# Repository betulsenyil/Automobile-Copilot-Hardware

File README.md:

# Automobile Copilot - Power & Motor Control System

This repository contains the hardware design files for an **Automobile Copilot System**. The project focuses on creating a reliable power management and motor actuation layer, specifically designed to handle the electrical environment of a vehicle.

## 📌 Project Overview
As a Computer Engineering student at Istanbul Sabahattin Zaim University, I developed this circuit to bridge the gap between high-level software logic and physical vehicle actuators. The board ensures clean power delivery to an Arduino Uno and provides safe control for DC motors.

## 🛠 Technical Specifications
- **Voltage Input:** +12V DC (Automotive battery compatible).
- **Voltage Regulation:** Integrated **LM2596** Switching Regulator (12V to 5V conversion).
- **Motor Driver:** **L298HN** Dual H-Bridge for bidirectional motor control.
- **Protection Circuits:**
  - **SMBJ16A TVS Diode:** Protects against transient voltage spikes common in vehicles.
  - **UF4007 Ultra-Fast Diodes:** Flyback protection against inductive back-EMF.
  - **Fused Input:** Integrated 1-2A fuse for overcurrent protection.

## 📂 File Structure
- [📄 Download Schematic PDF](https://github.com/betulsenyil/Automobile-Copilot-Hardware/blob/main/Copilot_Power_Motor_Board.kicad_pcb.pdf)
- `Hardware/Production_Files/`: Technical layer exports for manufacturing.
- `Copilot_Power_Motor_Board.kicad_sch`: Schematic source file.
- `Copilot_Power_Motor_Board.kicad_pcb`: PCB layout source file.

## 🚀 Technologies Used
- **Design Tool:** KiCad 9.0
- **Microcontroller:** Arduino Uno R3
- **Main Components:** LM2596, L298HN, TVS Protection.

## 📋 Future Work
- Integration of a CAN-Bus shield for vehicle data communication.
- Implementation of GPS and IMU sensors for co-pilot navigation logic.
- Development of the AI-driven co-pilot software in Python/C++.

---
*Developed by F. Betül Şenyıl*

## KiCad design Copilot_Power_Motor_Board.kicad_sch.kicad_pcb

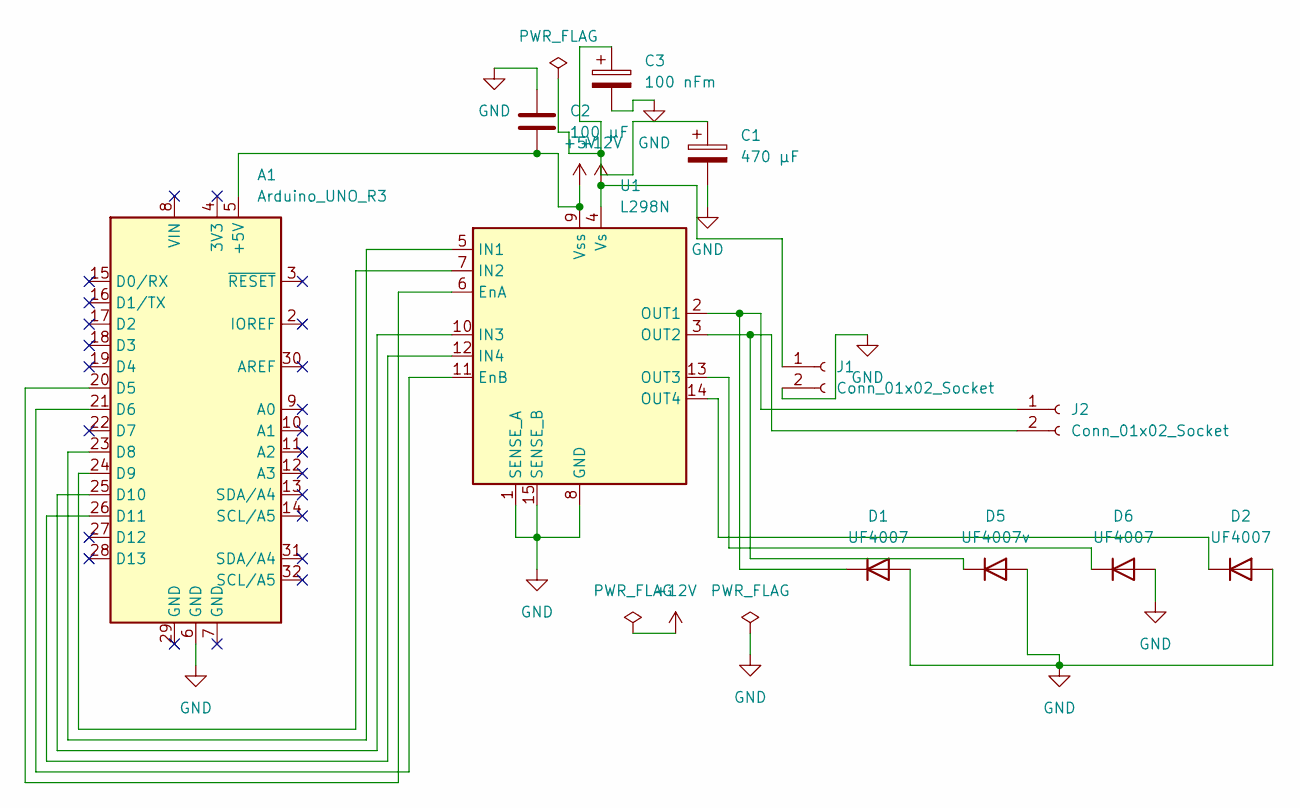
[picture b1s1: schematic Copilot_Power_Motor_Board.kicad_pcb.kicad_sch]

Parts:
A1: Arduino_UNO_R3
C1: 470 µF; D_5W_P10.16mm_Horizontal
C2: 100 µF; D_5W_P10.16mm_Horizontal
C3: 100 nFm; D_5W_P10.16mm_Horizontal
D1, D2, D6: UF4007; D_5W_P10.16mm_Horizontal
D5: UF4007v; D_5W_P10.16mm_Horizontal
J1, J2: Conn_01x02_Socket; D_5W_P10.16mm_Horizontal
U1: L298N; TO-220-15_P2.54x5.08mm_StaggerOdd_Lead4.58mm_Vertical

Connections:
+5V: A1.5 (+5V), C2.2, U1.9 (Vss)
+12V: J1.1, U1.4 (Vs)
GND: A1.6 (GND), C1.2, C2.1, C3.2, D1.2 (A), D2.2 (A), D5.2 (A), D6.2 (A), J1.2, U1.1 (SENSE_A), U1.8 (GND), U1.15 (SENSE_B)
unnamed: A1.20 (D5), U1.6 (EnA)
unnamed: A1.21 (D6), U1.11 (EnB)
unnamed: A1.23 (D8), U1.5 (IN1)
unnamed: A1.24 (D9), U1.7 (IN2)
unnamed: A1.25 (D10), U1.10 (IN3)
unnamed: A1.26 (D11), U1.12 (IN4)
unnamed: C1.1, C3.1
unnamed: D1.1 (K), J2.1, U1.2 (OUT1)
unnamed: D2.1 (K), U1.14 (OUT4)
unnamed: D5.1 (K), J2.2, U1.3 (OUT2)
unnamed: D6.1 (K), U1.13 (OUT3)

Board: 2 copper layers, 11 parts (0 on the bottom side), 14 nets, no tracks yet.

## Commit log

2026-04-23 Revise README for Automobile Copilot project
    Expanded README to include project overview, technical specifications, file structure, technologies used, and future work.
2026-04-23 Add schematic diagram in PDF format
2026-04-23 Rename Ekran görüntüsü 2026-04-23 233958.png to image_185048.png
2026-04-23 Enhance README with image and file structure updates
    Added a 3D render image and updated file structure details in the README.
2026-04-23 Refine file structure details in README.md
    Updated file structure section in README.md for clarity.
